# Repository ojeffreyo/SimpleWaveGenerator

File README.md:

# SimpleWaveGenerator
A simple sine-wave generator which frequency and amplitude controlled by outside 4-20mA small current.
The PCB is designed by KiCAD 6.0 version.

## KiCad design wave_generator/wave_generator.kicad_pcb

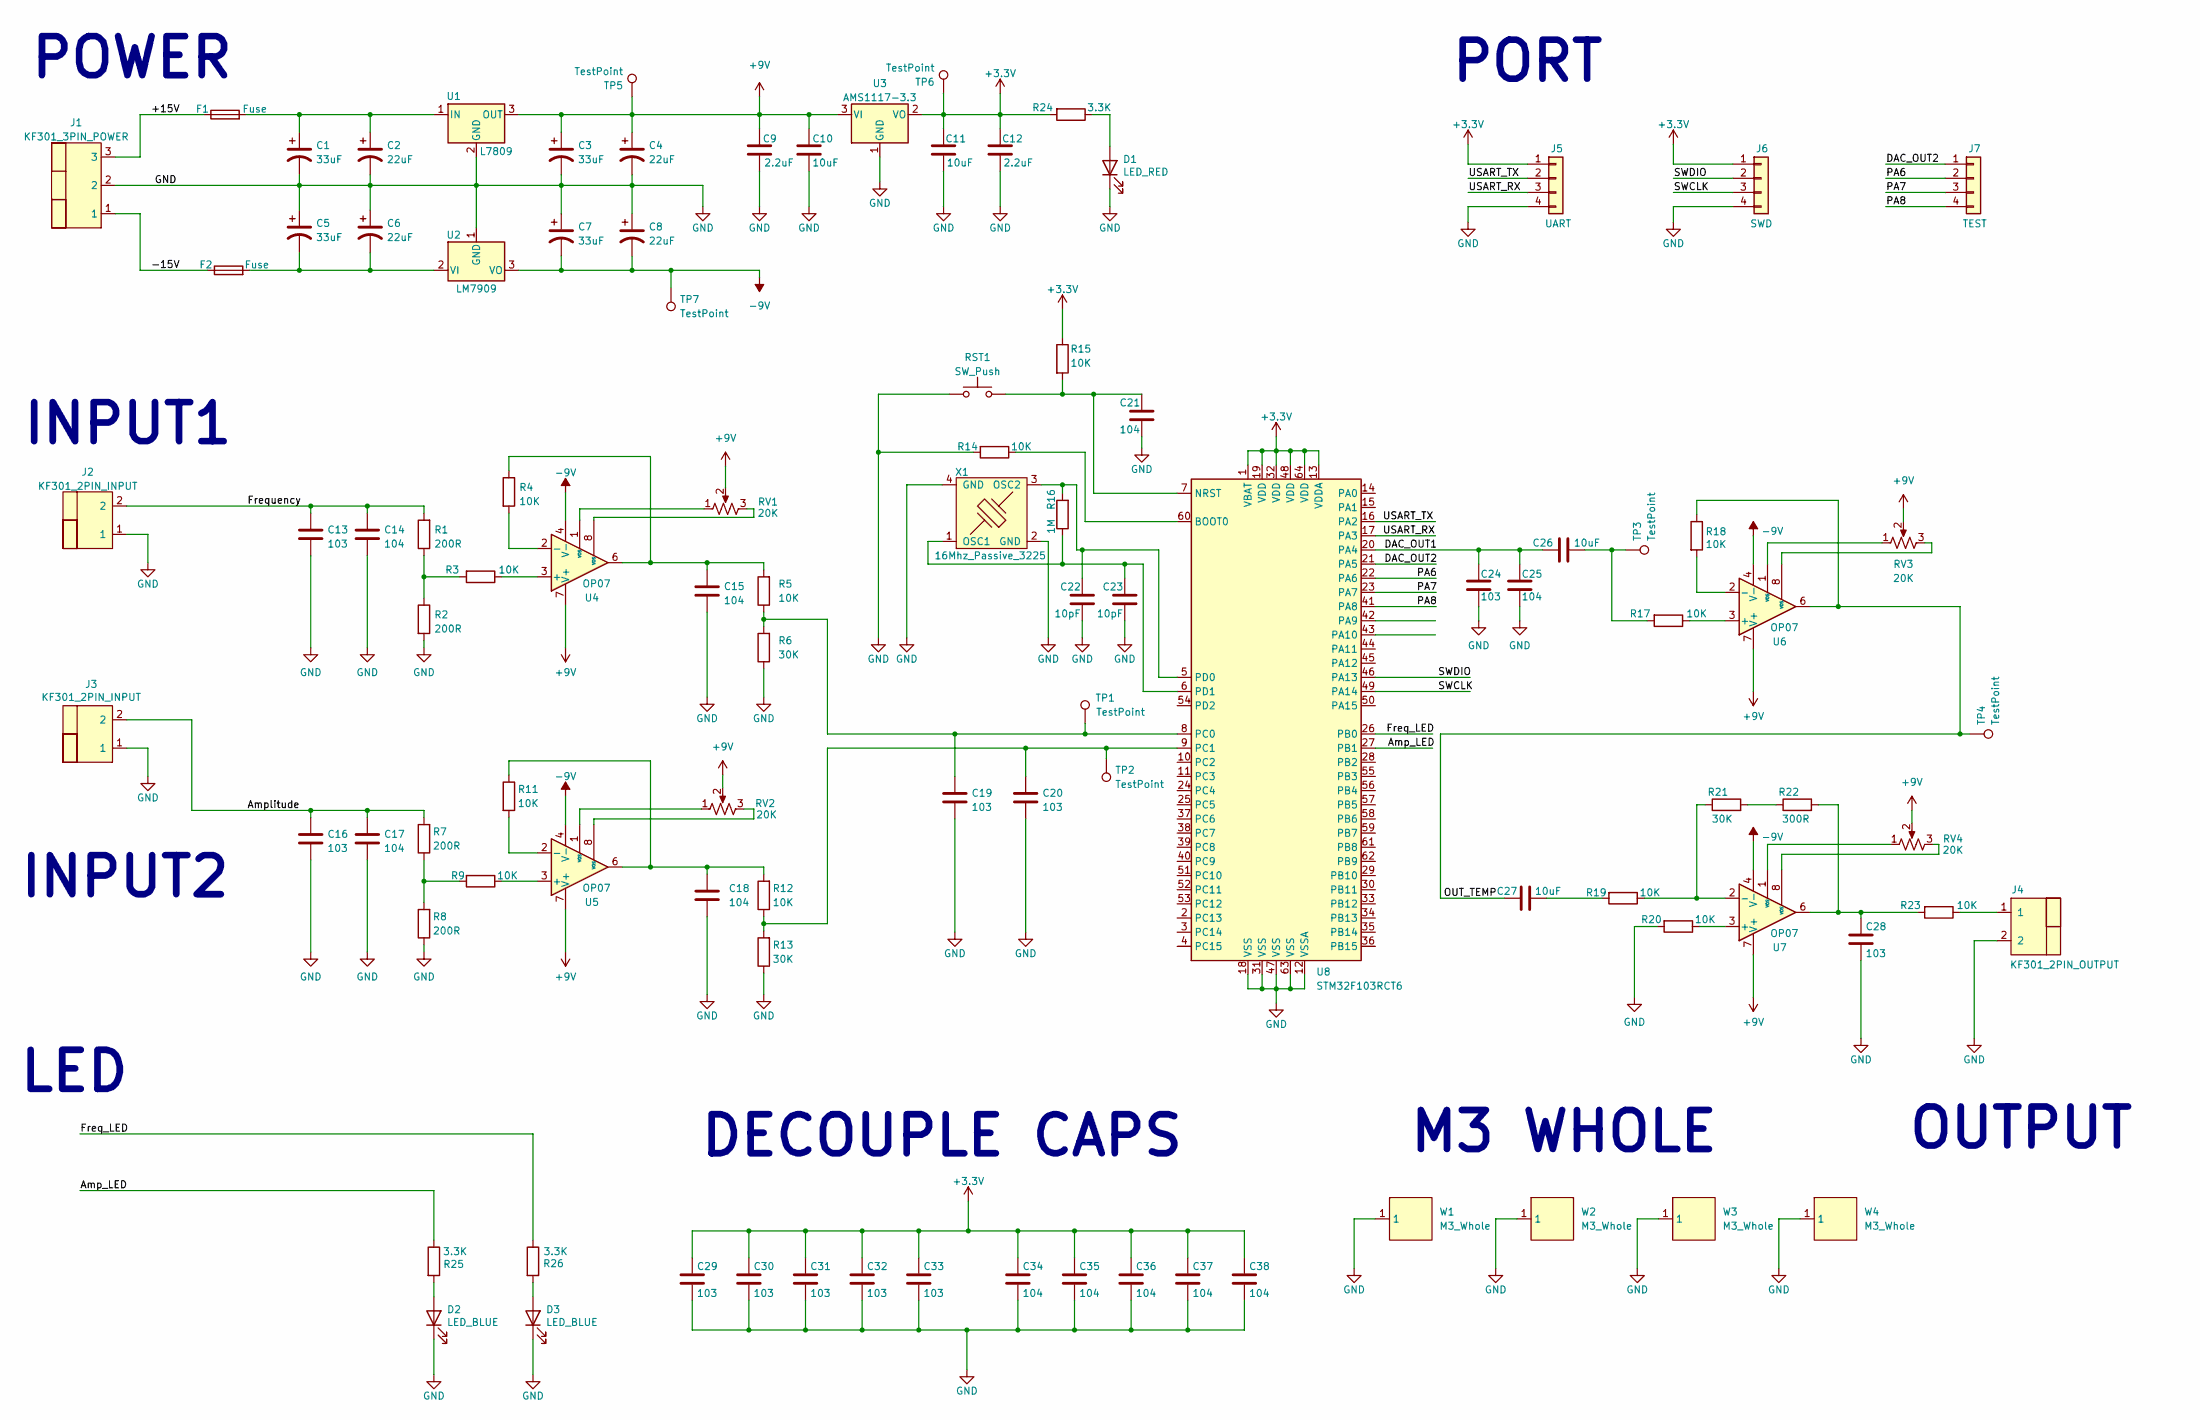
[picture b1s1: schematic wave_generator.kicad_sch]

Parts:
C1, C3, C5, C7: 33uF; CP_Elec_6.3x5.9
C2, C4, C6, C8: 22uF; CP_Elec_6.3x5.9
C9, C12: 2.2uF; C_0603_1608Metric
C10, C11, C26, C27: 10uF; C_0603_1608Metric
C13, C16, C19, C20, C24, C28, C29, C30, C31, C32, C33: 103; C_0603_1608Metric
C14, C15, C17, C18, C21, C25, C34, C35, C36, C37, C38: 104; C_0603_1608Metric
C22, C23: 10pF; C_0603_1608Metric
D1: LED_RED; LED_0603_1608Metric
D2, D3: LED_BLUE; LED_0603_1608Metric
F1, F2: Fuse; Fuse_1206_3216Metric
J1: KF301_3PIN_POWER; KF301-3P
J2, J3: KF301_2PIN_INPUT; KF301-2P
J4: KF301_2PIN_OUTPUT; KF301-2P
J5: UART; PinHeader_1x04_P2.54mm_Vertical
J6: SWD; PinHeader_1x04_P2.54mm_Vertical
J7: TEST; PinHeader_1x04_P2.54mm_Vertical
R1, R2, R7, R8: 200R; R_0603_1608Metric
R3, R4, R5, R9, R11, R12, R14, R15, R17, R18, R19, R20, R23: 10K; R_0603_1608Metric
R6, R13, R21: 30K; R_0603_1608Metric
R16: 1M; R_0603_1608Metric
R22: 300R; R_0603_1608Metric
R24, R25, R26: 3.3K; R_0603_1608Metric
RST1: SW_Push; SW_SPST_CK_RS282G05A3
RV1, RV2, RV3, RV4: 20K; R_Potential
TP1, TP2, TP3, TP4, TP5, TP6, TP7: TestPoint; Pin_D0.7mm_L6.5mm_W1.8mm_FlatFork
U1: L7809; TO-263-2
U2: LM7909; TO-263-2
U3: AMS1117-3.3; SOT-223-3_TabPin2
U4, U5, U6, U7: OP07; SOP-8_3.9x4.9mm_P1.27mm
U8: STM32F103RCT6; LQFP-64_10x10mm_P0.5mm
W1, W2, W3, W4: M3_Whole
X1: 16Mhz_Passive_3225; Oscillator_SMD_EuroQuartz_XO32-4Pin_3.2x2.5mm

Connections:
+3V3: C11.1, C12.1, C29.1, C30.1, C31.1, C32.1, C33.1, C34.1, C35.1, C36.1, C37.1, C38.1, J5.1, J6.1, R15.1, R24.2, TP6.1, U3.2 (VO), U8.1 (VBAT), U8.13 (VDDA), U8.19 (VDD), U8.32 (VDD), U8.48 (VDD), U8.64 (VDD)
+9V: C3.1, C4.1, C9.1, C10.1, RV1.2, RV2.2, RV3.2, RV4.2, TP5.1, U1.3 (OUT), U3.3 (VI), U4.7 (V+), U5.7 (V+), U6.7 (V+), U7.7 (V+)
-9V: C7.2, C8.2, TP7.1, U2.3 (VO), U4.4 (V-), U5.4 (V-), U6.4 (V-), U7.4 (V-)
/+15V: F1.1, J1.3
/-15V: F2.1, J1.1
/Amp_LED: R25.1, U8.27 (PB1)
/Amplitude: C16.1, C17.1, J3.2, R7.2
/DAC_OUT1: C24.1, C25.1, C26.1, U8.20 (PA4)
/DAC_OUT2: J7.1, U8.21 (PA5)
/Freq_LED: R26.1, U8.26 (PB0)
/Frequency: C13.1, C14.1, J2.2, R1.2
/OUT_TEMP: C27.1, R18.1, TP4.1, U6.6
/PA6: J7.2, U8.22 (PA6)
/PA7: J7.3, U8.23 (PA7)
/PA8: J7.4, U8.41 (PA8)
/SWCLK: J6.3, U8.49 (PA14)
/SWDIO: J6.2, U8.46 (PA13)
/USART_RX: J5.3, U8.17 (PA3)
/USART_TX: J5.2, U8.16 (PA2)
GND: C1.2, C2.2, C3.2, C4.2, C5.1, C6.1, C7.1, C8.1, C9.2, C10.2, C11.2, C12.2, C13.2, C14.2, C15.2, C16.2, C17.2, C18.2, C19.2, C20.2, C21.2, C22.2, C23.2, C24.2, C25.2, C28.2, C29.2, C30.2, C31.2, C32.2, C33.2, C34.2, C35.2, C36.2, C37.2, C38.2, D1.1 (K), D2.1 (K), D3.1 (K), J1.2, J2.1, J3.1, J4.2, J5.4, J6.4, R2.2, R6.1, R8.1, R13.1, R14.2, R20.2, RST1.1, U1.2 (GND), U2.1 (GND), U3.1 (GND), U8.12 (VSSA), U8.18 (VSS), U8.31 (VSS), U8.47 (VSS), U8.63 (VSS), W1.1, W2.1, W3.1, W4.1, X1.2 (GND), X1.4 (GND); also elsewhere on the board
unnamed: C1.1, C2.1, F1.2, U1.1 (IN)
unnamed: C5.2, C6.2, F2.2, U2.2 (VI)
unnamed: C15.1, R4.1, R5.2, U4.6
unnamed: C18.1, R11.1, R12.2, U5.6
unnamed: C19.1, R5.1, R6.2, TP1.1, U8.8 (PC0)
unnamed: C20.1, R12.1, R13.2, TP2.1, U8.9 (PC1)
unnamed: C21.1, R15.2, RST1.2, U8.7 (NRST)
unnamed: C22.1, R16.2, U8.5 (PD0), X1.3 (OSC2)
unnamed: C23.1, R16.1, U8.6 (PD1), X1.1 (OSC1)
unnamed: C26.2, R17.2, TP3.1
unnamed: C27.2, R19.2
unnamed: C28.1, R22.2, R23.2, U7.6
unnamed 32: D1.2 (A), R24.1; also elsewhere on the board
unnamed 33: D2.2 (A), R25.2; also elsewhere on the board
unnamed 34: D3.2 (A), R26.2; also elsewhere on the board
unnamed: J4.1, R23.1
unnamed: R1.1, R2.1, R3.2
unnamed: R3.1, U4.3 (+)
unnamed: R4.2, U4.2 (-)
unnamed: R7.1, R8.2, R9.2
unnamed: R9.1, U5.3 (+)
unnamed: R11.2, U5.2 (-)
unnamed: R14.1, U8.60 (BOOT0)
unnamed: R17.1, U6.3 (+)
unnamed: R18.2, U6.2 (-)
unnamed: R19.1, R21.1, U7.2 (-)
unnamed: R20.1, U7.3 (+)
unnamed: R21.2, R22.1
unnamed: RV1.1, U4.1 (VOS)
unnamed: RV1.3, U4.8 (VOS)
unnamed: RV2.1, U5.1 (VOS)
unnamed: RV2.3, U5.8 (VOS)
unnamed: RV3.1, U6.1 (VOS)
unnamed: RV3.3, U6.8 (VOS)
unnamed: RV4.1, U7.1 (VOS)
unnamed: RV4.3, U7.8 (VOS)

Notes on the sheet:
PORT
LED
DECOUPLE CAPS
POWER
INPUT1
OUTPUT
M3 WHOLE
INPUT2

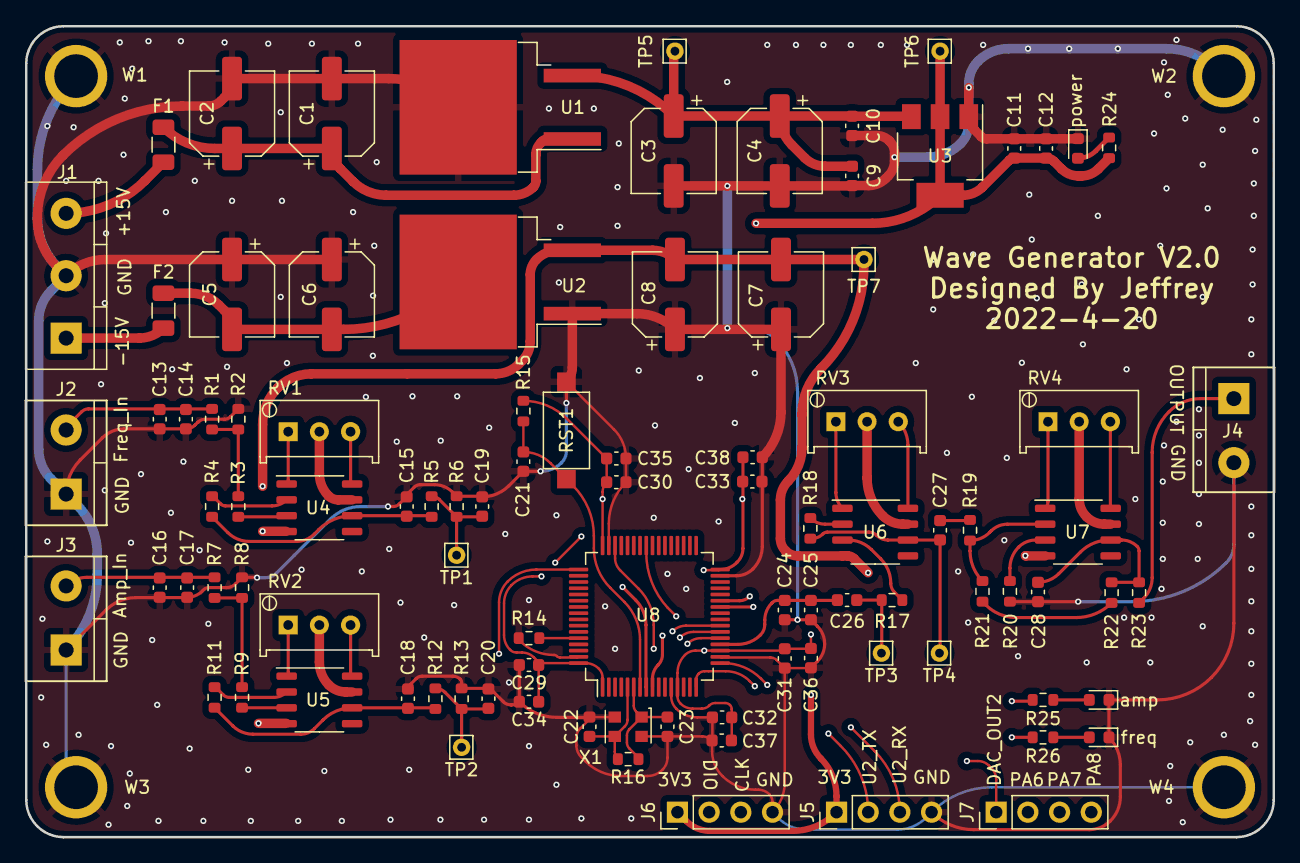
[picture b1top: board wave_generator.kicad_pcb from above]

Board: 4 copper layers, 100.0 x 65.0 mm, 100 parts (0 on the bottom side), 56 nets.

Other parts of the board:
amp: LED_BLUE; LED_0603_1608Metric
freq: LED_BLUE; LED_0603_1608Metric
power: LED_RED; LED_0603_1608Metric

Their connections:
GND: amp.1 (K), freq.1 (K), power.1 (K); also elsewhere on the board
unnamed 32: power.2 (A); also elsewhere on the board
unnamed 33: amp.2 (A); also elsewhere on the board
unnamed 34: freq.2 (A); also elsewhere on the board

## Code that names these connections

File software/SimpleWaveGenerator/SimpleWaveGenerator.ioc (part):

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Mcu.Name=STM32F103R(C-D-E)Tx
Mcu.Package=LQFP64
Mcu.UserName=STM32F103RCTx
PA13.Mode=Serial_Wire
PA13.Signal=SYS_JTMS-SWDIO
PA14.Mode=Serial_Wire
PA14.Signal=SYS_JTCK-SWCLK
PA2.Mode=Asynchronous
PA2.Signal=USART2_TX
PA3.Mode=Asynchronous
PA3.Signal=USART2_RX
PA4.Signal=COMP_DAC1_group
PA5.Signal=COMP_DAC2_group
PB0.GPIOParameters=GPIO_Speed,PinState
PB0.GPIO_Speed=GPIO_SPEED_FREQ_HIGH
PB0.PinState=GPIO_PIN_SET
PB0.Signal=GPIO_Output
PB1.GPIOParameters=GPIO_Speed,PinState
PB1.GPIO_Speed=GPIO_SPEED_FREQ_HIGH
PB1.PinState=GPIO_PIN_SET
PB1.Signal=GPIO_Output
PC0.Signal=ADCx_IN10
PC1.Signal=ADCx_IN11
PD0-OSC_IN.Mode=HSE-External-Oscillator
PD0-OSC_IN.Signal=RCC_OSC_IN
PD1-OSC_OUT.Mode=HSE-External-Oscillator
PD1-OSC_OUT.Signal=RCC_OSC_OUT
RCC.SYSCLKFreq_VALUE=72000000
RCC.SYSCLKSource=RCC_SYSCLKSOURCE_PLLCLK
board=custom

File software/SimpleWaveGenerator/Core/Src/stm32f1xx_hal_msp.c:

/* USER CODE BEGIN Header */
/**
  ******************************************************************************
  * @file         stm32f1xx_hal_msp.c
  * @brief        This file provides code for the MSP Initialization
  *               and de-Initialization codes.
  ******************************************************************************
  * @attention
  *
  * Copyright (c) 2022 STMicroelectronics.
  * All rights reserved.
  *
  * This software is licensed under terms that can be found in the LICENSE file
  * in the root directory of this software component.
  * If no LICENSE file comes with this software, it is provided AS-IS.
  *
  ******************************************************************************
  */
/* USER CODE END Header */

/* Includes ------------------------------------------------------------------*/
#include "main.h"
/* USER CODE BEGIN Includes */

/* USER CODE END Includes */

/* Private typedef -----------------------------------------------------------*/
/* USER CODE BEGIN TD */

/* USER CODE END TD */

/* Private define ------------------------------------------------------------*/
/* USER CODE BEGIN Define */

/* USER CODE END Define */

/* Private macro -------------------------------------------------------------*/
/* USER CODE BEGIN Macro */

/* USER CODE END Macro */

/* Private variables ---------------------------------------------------------*/
/* USER CODE BEGIN PV */

/* USER CODE END PV */

/* Private function prototypes -----------------------------------------------*/
/* USER CODE BEGIN PFP */

/* USER CODE END PFP */

/* External functions --------------------------------------------------------*/
/* USER CODE BEGIN ExternalFunctions */

/* USER CODE END ExternalFunctions */

/* USER CODE BEGIN 0 */

/* USER CODE END 0 */
/**
  * Initializes the Global MSP.
  */
void HAL_MspInit(void)
{
  /* USER CODE BEGIN MspInit 0 */

  /* USER CODE END MspInit 0 */

  __HAL_RCC_AFIO_CLK_ENABLE();
  __HAL_RCC_PWR_CLK_ENABLE();

  /* System interrupt init*/

  /** NOJTAG: JTAG-DP Disabled and SW-DP Enabled
  */
  __HAL_AFIO_REMAP_SWJ_NOJTAG();

  /* USER CODE BEGIN MspInit 1 */

  /* USER CODE END MspInit 1 */
}

/**
* @brief ADC MSP Initialization
* This function configures the hardware resources used in this example
* @param hadc: ADC handle pointer
* @retval None
*/
void HAL_ADC_MspInit(ADC_HandleTypeDef* hadc)
{
  GPIO_InitTypeDef GPIO_InitStruct = {0};
  if(hadc->Instance==ADC1)
  {
  /* USER CODE BEGIN ADC1_MspInit 0 */

  /* USER CODE END ADC1_MspInit 0 */
    /* Peripheral clock enable */
    __HAL_RCC_ADC1_CLK_ENABLE();

    __HAL_RCC_GPIOC_CLK_ENABLE();
    /**ADC1 GPIO Configuration
    PC0     ------> ADC1_IN10
    */
    GPIO_InitStruct.Pin = GPIO_PIN_0;
    GPIO_InitStruct.Mode = GPIO_MODE_ANALOG;
    HAL_GPIO_Init(GPIOC, &GPIO_InitStruct);

  /* USER CODE BEGIN ADC1_MspInit 1 */

  /* USER CODE END ADC1_MspInit 1 */
  }
  else if(hadc->Instance==ADC2)
  {
  /* USER CODE BEGIN ADC2_MspInit 0 */

  /* USER CODE END ADC2_MspInit 0 */
    /* Peripheral clock enable */
    __HAL_RCC_ADC2_CLK_ENABLE();

    __HAL_RCC_GPIOC_CLK_ENABLE();
    /**ADC2 GPIO Configuration
    PC1     ------> ADC2_IN11
    */
    GPIO_InitStruct.Pin = GPIO_PIN_1;
    GPIO_InitStruct.Mode = GPIO_MODE_ANALOG;
    HAL_GPIO_Init(GPIOC, &GPIO_InitStruct);

  /* USER CODE BEGIN ADC2_MspInit 1 */

  /* USER CODE END ADC2_MspInit 1 */
  }

}

/**
* @brief ADC MSP De-Initialization
* This function freeze the hardware resources used in this example
* @param hadc: ADC handle pointer
* @retval None
*/
void HAL_ADC_MspDeInit(ADC_HandleTypeDef* hadc)
{
  if(hadc->Instance==ADC1)
  {
  /* USER CODE BEGIN ADC1_MspDeInit 0 */

  /* USER CODE END ADC1_MspDeInit 0 */
    /* Peripheral clock disable */
    __HAL_RCC_ADC1_CLK_DISABLE();

    /**ADC1 GPIO Configuration
    PC0     ------> ADC1_IN10
    */
    HAL_GPIO_DeInit(GPIOC, GPIO_PIN_0);

  /* USER CODE BEGIN ADC1_MspDeInit 1 */

  /* USER CODE END ADC1_MspDeInit 1 */
  }
  else if(hadc->Instance==ADC2)
  {
  /* USER CODE BEGIN ADC2_MspDeInit 0 */

  /* USER CODE END ADC2_MspDeInit 0 */
    /* Peripheral clock disable */
    __HAL_RCC_ADC2_CLK_DISABLE();

    /**ADC2 GPIO Configuration
    PC1     ------> ADC2_IN11
    */
    HAL_GPIO_DeInit(GPIOC, GPIO_PIN_1);

  /* USER CODE BEGIN ADC2_MspDeInit 1 */

  /* USER CODE END ADC2_MspDeInit 1 */
  }

}

/**
* @brief DAC MSP Initialization
* This function configures the hardware resources used in this example
* @param hdac: DAC handle pointer
* @retval None
*/
void HAL_DAC_MspInit(DAC_HandleTypeDef* hdac)
{
  GPIO_InitTypeDef GPIO_InitStruct = {0};
  if(hdac->Instance==DAC)
  {
  /* USER CODE BEGIN DAC_MspInit 0 */

  /* USER CODE END DAC_MspInit 0 */
    /* Peripheral clock enable */
    __HAL_RCC_DAC_CLK_ENABLE();

    __HAL_RCC_GPIOA_CLK_ENABLE();
    /**DAC GPIO Configuration
    PA4     ------> DAC_OUT1
    PA5     ------> DAC_OUT2
    */
    GPIO_InitStruct.Pin = GPIO_PIN_4|GPIO_PIN_5;
    GPIO_InitStruct.Mode = GPIO_MODE_ANALOG;
    HAL_GPIO_Init(GPIOA, &GPIO_InitStruct);

  /* USER CODE BEGIN DAC_MspInit 1 */

  /* USER CODE END DAC_MspInit 1 */
  }

}

/**
* @brief DAC MSP De-Initialization
* This function freeze the hardware resources used in this example
* @param hdac: DAC handle pointer
* @retval None
*/
void HAL_DAC_MspDeInit(DAC_HandleTypeDef* hdac)
{
  if(hdac->Instance==DAC)
  {
  /* USER CODE BEGIN DAC_MspDeInit 0 */

  /* USER CODE END DAC_MspDeInit 0 */
    /* Peripheral clock disable */
    __HAL_RCC_DAC_CLK_DISABLE();

    /**DAC GPIO Configuration
    PA4     ------> DAC_OUT1
    PA5     ------> DAC_OUT2
    */
    HAL_GPIO_DeInit(GPIOA, GPIO_PIN_4|GPIO_PIN_5);

  /* USER CODE BEGIN DAC_MspDeInit 1 */

  /* USER CODE END DAC_MspDeInit 1 */
  }

}

/**
* @brief TIM_Base MSP Initialization
* This function configures the hardware resources used in this example
* @param htim_base: TIM_Base handle pointer
* @retval None
*/
void HAL_TIM_Base_MspInit(TIM_HandleTypeDef* htim_base)
{
  if(htim_base->Instance==TIM1)
  {
  /* USER CODE BEGIN TIM1_MspInit 0 */

  /* USER CODE END TIM1_MspInit 0 */
    /* Peripheral clock enable */
    __HAL_RCC_TIM1_CLK_ENABLE();
    /* TIM1 interrupt Init */
    HAL_NVIC_SetPriority(TIM1_UP_IRQn, 0, 0);
    HAL_NVIC_EnableIRQ(TIM1_UP_IRQn);
  /* USER CODE BEGIN TIM1_MspInit 1 */

  /* USER CODE END TIM1_MspInit 1 */
  }

}

/**
* @brief TIM_Base MSP De-Initialization
* This function freeze the hardware resources used in this example
* @param htim_base: TIM_Base handle pointer
* @retval None
*/
void HAL_TIM_Base_MspDeInit(TIM_HandleTypeDef* htim_base)
{
  if(htim_base->Instance==TIM1)
  {
  /* USER CODE BEGIN TIM1_MspDeInit 0 */

  /* USER CODE END TIM1_MspDeInit 0 */
    /* Peripheral clock disable */
    __HAL_RCC_TIM1_CLK_DISABLE();

    /* TIM1 interrupt DeInit */
    HAL_NVIC_DisableIRQ(TIM1_UP_IRQn);
  /* USER CODE BEGIN TIM1_MspDeInit 1 */

  /* USER CODE END TIM1_MspDeInit 1 */
  }

}

/**
* @brief UART MSP Initialization
* This function configures the hardware resources used in this example
* @param huart: UART handle pointer
* @retval None
*/
void HAL_UART_MspInit(UART_HandleTypeDef* huart)
{
  GPIO_InitTypeDef GPIO_InitStruct = {0};
  if(huart->Instance==USART2)
  {
  /* USER CODE BEGIN USART2_MspInit 0 */

  /* USER CODE END USART2_MspInit 0 */
    /* Peripheral clock enable */
    __HAL_RCC_USART2_CLK_ENABLE();

    __HAL_RCC_GPIOA_CLK_ENABLE();
    /**USART2 GPIO Configuration
    PA2     ------> USART2_TX
    PA3     ------> USART2_RX
    */
    GPIO_InitStruct.Pin = GPIO_PIN_2;
    GPIO_InitStruct.Mode = GPIO_MODE_AF_PP;
    GPIO_InitStruct.Speed = GPIO_SPEED_FREQ_HIGH;
    HAL_GPIO_Init(GPIOA, &GPIO_InitStruct);

    GPIO_InitStruct.Pin = GPIO_PIN_3;
    GPIO_InitStruct.Mode = GPIO_MODE_INPUT;
    GPIO_InitStruct.Pull = GPIO_NOPULL;
    HAL_GPIO_Init(GPIOA, &GPIO_InitStruct);

  /* USER CODE BEGIN USART2_MspInit 1 */

  /* USER CODE END USART2_MspInit 1 */
  }

}

/**
* @brief UART MSP De-Initialization
* This function freeze the hardware resources used in this example
* @param huart: UART handle pointer
* @retval None
*/
void HAL_UART_MspDeInit(UART_HandleTypeDef* huart)
{
  if(huart->Instance==USART2)
  {
  /* USER CODE BEGIN USART2_MspDeInit 0 */

  /* USER CODE END USART2_MspDeInit 0 */
    /* Peripheral clock disable */
    __HAL_RCC_USART2_CLK_DISABLE();

    /**USART2 GPIO Configuration
    PA2     ------> USART2_TX
    PA3     ------> USART2_RX
    */
    HAL_GPIO_DeInit(GPIOA, GPIO_PIN_2|GPIO_PIN_3);

  /* USER CODE BEGIN USART2_MspDeInit 1 */

  /* USER CODE END USART2_MspDeInit 1 */
  }

}

/* USER CODE BEGIN 1 */

/* USER CODE END 1 */

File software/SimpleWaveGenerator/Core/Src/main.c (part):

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/*offset*/
unsigned short offset = 2000;

unsigned short amplitude = 0;
unsigned short frequency = 0;
unsigned short frequency_step = 0;
	
/*important variable*/
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  /*Configure GPIO pin Output Level */
  HAL_GPIO_WritePin(GPIOB, GPIO_PIN_0|GPIO_PIN_1, GPIO_PIN_SET);

  /*Configure GPIO pins : PB0 PB1 */
  GPIO_InitStruct.Pin = GPIO_PIN_0|GPIO_PIN_1;
  GPIO_InitStruct.Mode = GPIO_MODE_OUTPUT_PP;
  GPIO_InitStruct.Pull = GPIO_NOPULL;
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
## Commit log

2022-04-06 2022-4-6 PCB Design did not start yet.
2022-04-11 pcb not finished yet
2022-04-12 Finished PCB
2022-04-18 finished the initialization
2022-04-24 fixed hardware error
2022-04-24 generated gerber files
2022-04-24 gerber files
2022-04-24 new version V2.0
2022-04-24 sin wave generated nicely
2022-04-25 Sin wave generated.
2022-04-25 adjustable sin wave frequency
2022-04-25 adjustable amplitude
2022-04-29 updated version
2022-05-05 40Hz-130Hz not very stable
2022-05-06 linearized the parameter
2022-05-10 define the upper limit of the function
2022-11-06 Added new box model
2022-11-06 add 3D models for the Box
